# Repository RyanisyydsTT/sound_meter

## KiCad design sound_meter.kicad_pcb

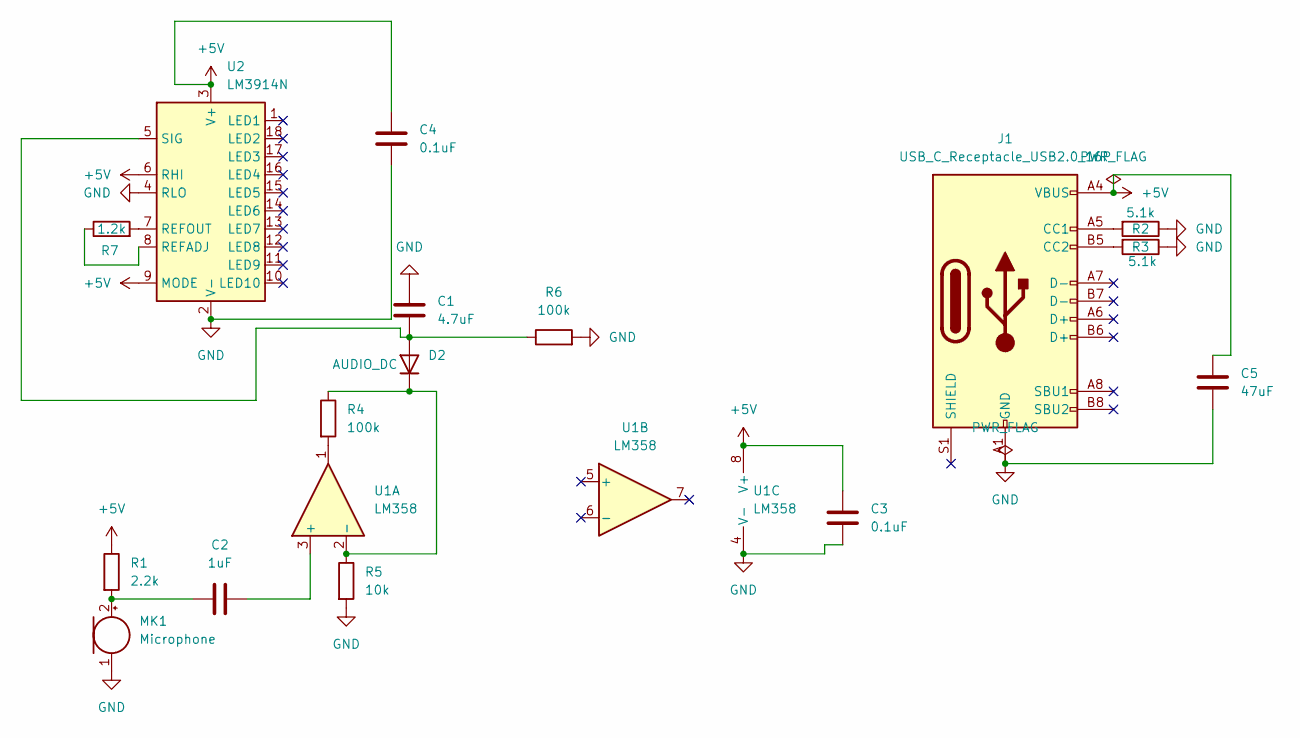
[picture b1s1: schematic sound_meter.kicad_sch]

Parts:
C1: 4.7uF; C_Disc_D5.0mm_W2.5mm_P5.00mm
C2: 1uF; C_Disc_D5.0mm_W2.5mm_P5.00mm
C3, C4: 0.1uF; C_Disc_D5.0mm_W2.5mm_P5.00mm
C5: 47uF; C_Radial_D6.3mm_H5.0mm_P2.50mm
D2: AUDIO_DC; D_DO-35_SOD27_P7.62mm_Horizontal
J1: USB_C_Receptacle_USB2.0_16P; USB_C_Receptacle_GCT_USB4085
MK1: Microphone; PinHeader_1x02_P2.54mm_Horizontal
R1: 2.2k; R_Axial_DIN0207_L6.3mm_D2.5mm_P7.62mm_Horizontal
R2, R3: 5.1k; R_Axial_DIN0207_L6.3mm_D2.5mm_P7.62mm_Horizontal
R4, R6: 100k; R_Axial_DIN0207_L6.3mm_D2.5mm_P7.62mm_Horizontal
R5: 10k; R_Axial_DIN0207_L6.3mm_D2.5mm_P7.62mm_Horizontal
R7: 1.2k; R_Axial_DIN0207_L6.3mm_D2.5mm_P7.62mm_Horizontal
U1: LM358; DIP-8_W7.62mm
U2: LM3914N; DIP-18_W7.62mm

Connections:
+5V: C3.1, C4.1, C5.1, J1.A4 (VBUS), J1.A9 (VBUS), J1.B4 (VBUS), J1.B9 (VBUS), R1.1, U1.8 (V+), U2.3 (V+), U2.6 (RHI), U2.9 (MODE)
GND: C1.1, C3.2, C4.2, C5.2, J1.A1 (GND), J1.A12 (GND), J1.B1 (GND), J1.B12 (GND), MK1.1 (-), R2.1, R3.1, R5.2, R6.2, U1.4 (V-), U2.2 (V-), U2.4 (RLO)
unnamed: C1.2, D2.2 (A), R6.1, U2.5 (SIG)
unnamed: D2.1 (K), R4.1, R5.1, U1.2 (-)
unnamed: J1.A5 (CC1), R2.2
unnamed: J1.B5 (CC2), R3.2
unnamed: C2.2, MK1.2 (+), R1.2
unnamed: R4.2, U1.1
unnamed: C2.1, U1.3 (+)
unnamed: R7.1, U2.8 (REFADJ)
unnamed: R7.2, U2.7 (REFOUT)

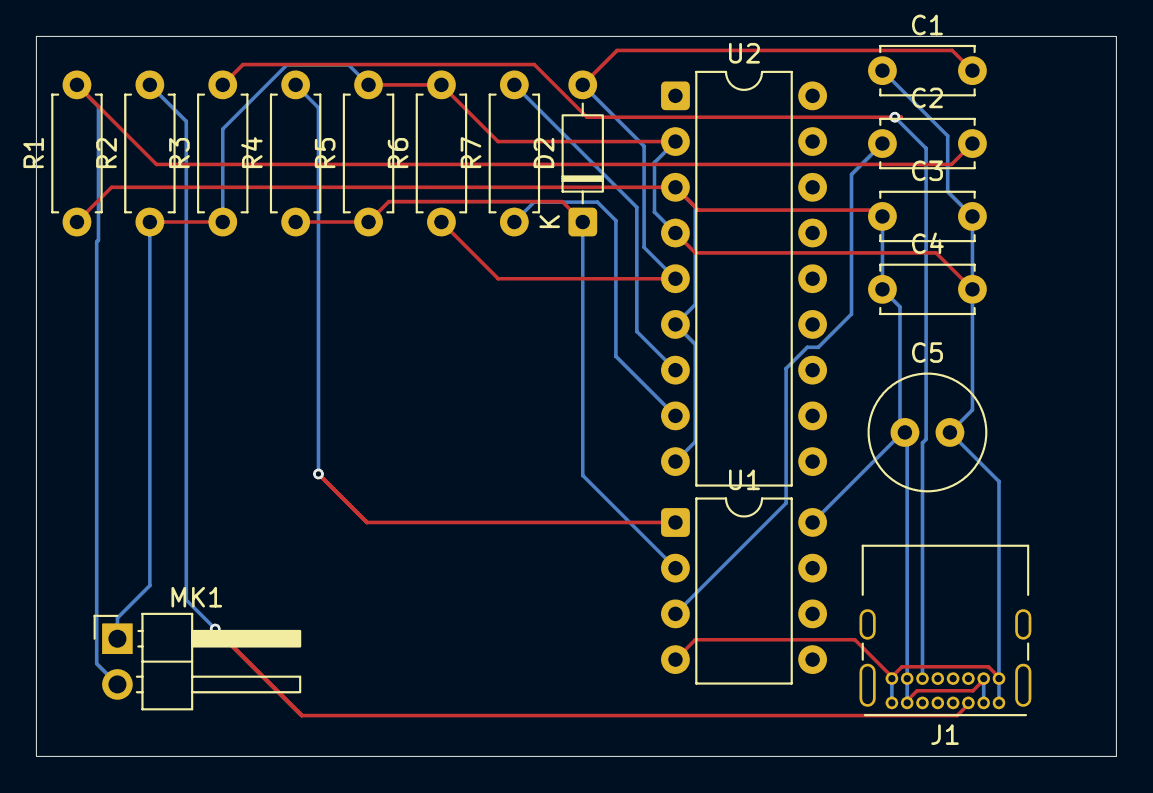
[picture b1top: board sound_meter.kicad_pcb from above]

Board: 2 copper layers, 60.0 x 40.0 mm, 17 parts (0 on the bottom side), 11 nets.

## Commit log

2026-03-15 Create LICENSE
